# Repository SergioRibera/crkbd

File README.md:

# Corne keyboard

The Corne keyboard is a split keyboard with 3x6 column staggered keys
and 3 thumb keys, based on [Helix](https://github.com/MakotoKurauchi/helix).
Crkbd stands for Corne Keyboard.

## Latest versions
- corne-cherry: for Cherry MX compatible switches

  - v4 Hotswappable ([JP](docs/corne-cherry/v4/buildguide_jp.md)/[EN](docs/corne-cherry/v4/buildguide_en.md))
  - v4 Soldering (will be released)
- corne-chocolate: for Kailh choc v1 and v2 switches
  - v4 Hotswappable ([JP](docs/corne-chocolate/v4/buildguide_jp.md)/[EN](docs/corne-chocolate/v4/buildguide_en.md)):
  - v4 Soldering (will be released)

- [Corne v4 Cherry Wireless](./pcbs/cherry-wireless)

## Old versions

- corne-classic: for Cherry MX compatible switches 
  - v1 Soldering: ([JP](docs/corne-classic/buildguide_jp.md)/[EN](docs/corne-classic/buildguide_en.md))
- corne-cherry: for Cherry MX compatible switches
  - v2 Hotswappable: ([JP](docs/corne-cherry/v2/buildguide_jp.md)/[EN](docs/corne-cherry/v2/buildguide_en.md))
  - v2 Hotswappable tilting version: ([tilting, JP](docs/corne-cherry/v2/buildguide_tilting_tenting_plate_jp.md)/[tilting, EN](docs/corne-cherry/v2/buildguide_tilting_tenting_plate_en.md)):
  - v3 Hotswappable: ([JP](docs/corne-cherry/v3/buildguide_jp.md)/[EN](docs/corne-cherry/v3/buildguide_en.md))
- corne-chocolate: for Kailh choc v1 switches
  - v2 Hotswappable: ([JP](docs/corne-chocolate/v2/buildguide_jp.md)/[EN](docs/corne-chocolate/v2/buildguide_en.md)):
- corne-light: for easy build with a simple PCB
  - v1 Soldering: ([JP](docs/corne-light/v1/buildguide_jp.md)/[EN](docs/corne-light/v1/buildguide_en.md)):
  - v2 Soldering: ([JP](docs/corne-light/v2/buildguide_low_edition_jp.md)/[EN](docs/corne-light/v2/buildguide_low_edition_en.md)):

## Images

### Cherry

### Chocolate

### Drawing

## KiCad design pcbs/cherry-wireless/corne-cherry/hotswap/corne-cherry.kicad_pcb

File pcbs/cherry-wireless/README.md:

# Corne Keyboard Wireless Fork

This project is a customized fork of the popular Corne ergonomic keyboard.

> [!NOTE]
> As soon as I have my build I will upload pictures of the finished keyboard.

## Disclaimer

> [!IMPORTANT]
> **⚠️ IMPORTANT NOTICE: I am not an electronics expert ⚠️**
>
> This project has been carried out with the help of a professional contracted through Fiverr.
> If you have specific technical questions, I recommend consulting an expert.
>
> https://fiverr.com/pcbdesign_engr

## Features

- Custom layout based on the original Corne
- Hotswap Sockets
- Sk6812MiniE RGB LED per switch
- NRF52840-QIAA-R7 Microcontroller
- Differential pair routing from USB to MCU
- TypeC USB
- NiceView connector
- Removed extra keys added in v4
- Removed TRRS?

> [!NOTE]
> According to the engineer in charge, all components available at LCSC JLCPCB were used.

## Project Images

## Acknowledgements

This project would not have been possible without the help of a talented Fiverr professional. You can find their profile here: https://fiverr.com/pcbdesign_engr

I would also like to thank the original Corne Keyboard community for their incredible work and for inspiring this project.

## License

Use it as you wish, subject to the license of the original project.

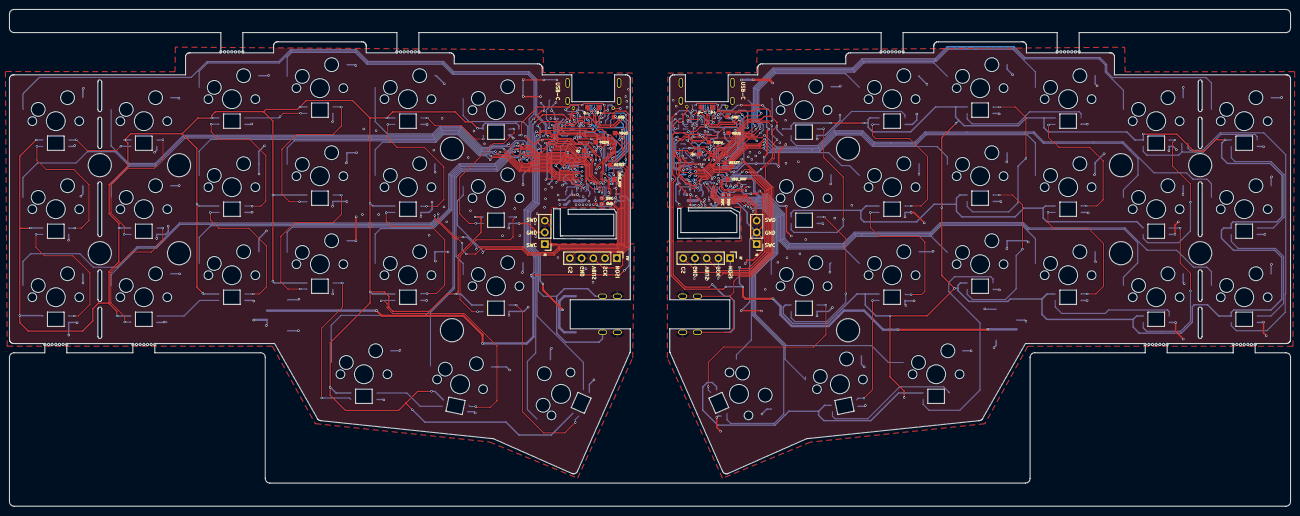
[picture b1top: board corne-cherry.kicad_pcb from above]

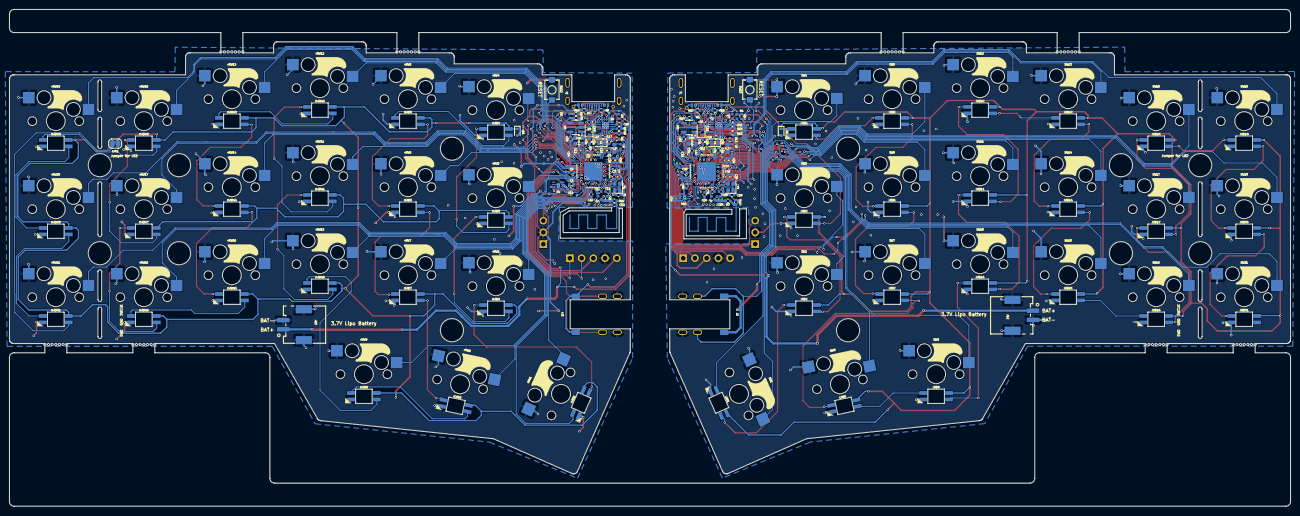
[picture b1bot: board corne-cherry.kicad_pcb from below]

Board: 2 copper layers, 277.2 x 107.5 mm, 233 parts (201 on the bottom side), 179 nets.

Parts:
AE1, AE2: Antenna; 2.4GHz-meander-antenna-v2
BT1, BT2, BT3, BT4: Breakaway Tabs; Breakaway_Tabs
C1, C13, C14, C20, C24, C25, C26, C35, C36, C41, C46, C50, C51, C52: 4.7uF; C_0402_1005Metric
C2, C3, C4, C10, C19, C32, C42, C43, C44, C45: 100nF; C_0402_1005Metric
C5, C9, C28, C31: 1pF; C_0402_1005Metric
C6, C7, C17, C18, C29, C30, C39, C40: 15pF; C_0402_1005Metric
C8, C15, C23, C37, C47, C49: 1uF; C_0402_1005Metric
C11, C33: 100pF; C_0402_1005Metric
C12, C34: 1nF; C_0402_1005Metric
C16, C38: 47nF; C_0402_1005Metric
C21, C48: 10uF; C_0603_1608Metric
C22, C27: 1.5pF; C_0402_1005Metric
D1: 1N4148WT; D_SOD-523
D2, D4: BLUE; LED_0402_1005Metric
D3, D7: ORANGE; LED_0402_1005Metric
D5, D6: PMEG4010CEJ; D_SOD-323F
J1, J7: USB_C_Receptacle_USB2.0; USB-C_C168688
J2: TRS; PJ-398A-5A_PJ-399B-6A
J3, J11: Screw_Terminal_01x05; PinHeader_1x05_P2.54mm_Vertical
J4, J5, J9, J10: PTH; PTH-0.8_0.45mm
J6, J8: Conn_01x03; PinHeader_1x03_P2.54mm_Vertical
J12, J13: Conn_01x02_Shielded; CONN-SMD_SM02B-PASS-TLFSN
L1, L5: 3.9nH; L_0402_1005Metric
L2, L6: 15nH; L_0402_1005Metric
L3, L4, L7, L8: 10uH; L_0603_1608Metric
LED1, LED2, LED3, LED4, LED5, LED6, LED7, LED8, LED9, LED10, LED11, LED12, LED13, LED14, LED15, LED16, LED17, LED18, LED19, LED20, LED21: YS-SK6812MINI-E; YS-SK6812MINI-E_crone
NT1, NT2: NetTie_2; net-tie-2-tiny
R1, R13: 3.9k; R_0402_1005Metric
R2, R14: 2M; R_0402_1005Metric
R3, R11: 0R; R_0402_1005Metric
R4, R5: 1.5k; R_0402_1005Metric
R6, R7, R8, R12, R15, R18: 10k; R_0402_1005Metric
R9, R10, R16, R17: 5.1k; R_0402_1005Metric
SW1: SW_Push; keyswitch_cherrymx_hotswap_1.5u
SW2, SW3, SW4, SW5, SW6, SW7, SW8, SW9, SW10, SW11, SW12, SW13, SW14, SW15, SW16, SW17, SW18, SW19, SW20, SW21: SW_Push; keyswitch_cherrymx_hotswap_1u
SW22, SW23: SW_SPST; SW-SMD-TS-1088-AR02016
TP1, TP2, TP3, TP4, TP5, TP6, TP7, TP8, TP9, TP10, TP11, TP12, TP13, TP14, TP15, TP16, TP17, TP18, TP19, TP20: PAD; TestPoint_Pad_1.0x1.0mm-nosilk
U1, U4: NRF52840-QIAA-R7; AQFN-73-1EP_7x7mm_P0.5mm_NRF52840-custom
U2, U7: BQ24075RGT; VQFN-16-1EP_3x3mm_P0.5mm_EP1.6x1.6mm
U3, U8: XC6220B331MR; TSOT-23-5
U5, U9: ESDR0502NMUTAG; UDFN-6_1.2x1.0mm_P0.4mm
U6, U10: MAX17048; TDFN-8-1EP_2x2mm_P0.5mm_EP0.8x1.2mm
Y1, Y3: 32MHz; Crystal_SMD_2016-4Pin_2.0x1.6mm
Y2, Y4: 32.768 kHz; Crystal_SMD_2012-2Pin_2.0x1.2mm
rBT1, rBT2, rBT3, rBT4: Breakaway Tabs; Breakaway_Tabs
rD1: 1N4148WT; D_SOD-523
rJ2: TRS; PJ-398A-5A_PJ-399B-6A
rJP1: SolderJumper_2_Bridged; SolderJumper-2_P1.3mm_Open_RoundedPad1.0x1.5mm
rLED1, rLED2, rLED3, rLED4, rLED5, rLED6, rLED7, rLED8, rLED9, rLED10, rLED11, rLED12, rLED13, rLED14, rLED15, rLED16, rLED17, rLED18, rLED19, rLED20, rLED21: YS-SK6812MINI-E; YS-SK6812MINI-E_crone
rSW1: SW_Push; keyswitch_cherrymx_hotswap_1.5u
rSW2, rSW3, rSW4, rSW5, rSW6, rSW7, rSW8, rSW9, rSW10, rSW11, rSW12, rSW13, rSW14, rSW15, rSW16, rSW17, rSW18, rSW19, rSW20, rSW21: SW_Push; keyswitch_cherrymx_hotswap_1u

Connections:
/left/ANT_L: AE2.1 (A), C27.2, R3.2
/left/CC1: J7.A5 (CC1), R16.1
/left/CC2: J7.B5 (CC2), R17.1
/left/KEY1_L: SW1.1, U4.AC21 (P0.25)
/left/KEY2_L: SW2.1, U4.T23 (P1.05)
/left/KEY3_L: SW3.1, U4.AD18 (P0.22)
/left/KEY4_L: SW4.1, U4.A8 (AIN7/P0.31)
/left/KEY5_L: SW5.1, U4.A10 (AIN5/P0.29)
/left/KEY6_L: SW6.1, U4.A20 (P1.10)
/left/KEY7_L: SW7.1, U4.R24 (P1.06)
/left/KEY8_L: SW8.1, U4.V23 (P1.03)
/left/KEY9_L: SW9.1, U4.P23 (P1.07)
/left/KEY10_L: SW10.1, U4.U24 (P1.04)
/left/KEY11_L: SW11.1, U4.B19 (P1.11)
/left/KEY12_L: SW12.1, U4.A12 (AIN0/P0.02)
/left/KEY13_L: SW13.1, U4.U1 (TRACEDATA1/P0.12)
/left/KEY14_L: SW14.1, U4.B17 (P1.12)
/left/KEY15_L: SW15.1, U4.W24 (P1.02)
/left/KEY16_L: SW16.1, U4.AD22 (TRACEDATA0/P1.00)
/left/KEY17_L: SW17.1, U4.A16 (P1.13)
/left/KEY18_L: SW18.1, U4.B9 (AIN6/P0.30)
/left/KEY19_L: SW19.1, U4.P2 (P1.08)
/left/KEY20_L: SW20.1, U4.B13 (AIN1/P0.03)
/left/KEY21_L: SW21.1, U4.AD20 (P0.24)
/left/RGBLEDs_L: LED1.4 (DIN), U4.Y23 (P1.01)
/right/ANT_R: AE1.1 (A), C22.2, R11.2
/right/CC1: J1.A5 (CC1), R9.1
/right/CC2: J1.B5 (CC2), R10.1
/right/KEY1_R: U1.AC21 (P0.25), rSW1.1
/right/KEY2_R: U1.T23 (P1.05), rSW2.1
/right/KEY3_R: U1.AD18 (P0.22), rSW3.1
/right/KEY4_R: U1.A8 (AIN7/P0.31), rSW4.1
/right/KEY5_R: U1.A10 (AIN5/P0.29), rSW5.1
/right/KEY6_R: U1.A20 (P1.10), rSW6.1
/right/KEY7_R: U1.R24 (P1.06), rSW7.1
/right/KEY8_R: U1.V23 (P1.03), rSW8.1
/right/KEY9_R: U1.P23 (P1.07), rSW9.1
/right/KEY10_R: U1.U24 (P1.04), rSW10.1
/right/KEY11_R: U1.B19 (P1.11), rSW11.1
/right/KEY12_R: U1.A12 (AIN0/P0.02), rSW12.1
/right/KEY13_R: U1.U1 (TRACEDATA1/P0.12), rSW13.1
/right/KEY14_R: U1.B17 (P1.12), rSW14.1
/right/KEY15_R: U1.W24 (P1.02), rSW15.1
/right/KEY16_R: U1.AD22 (TRACEDATA0/P1.00), rSW16.1
/right/KEY17_R: U1.A16 (P1.13), rSW17.1
/right/KEY18_R: U1.B9 (AIN6/P0.30), rSW18.1
/right/KEY19_R: U1.P2 (P1.08), rSW19.1
/right/KEY20_R: U1.B13 (AIN1/P0.03), rSW20.1
/right/KEY21_R: U1.AD20 (P0.24), rSW21.1
/right/RGBLEDs_R: U1.Y23 (P1.01), rLED1.4 (DIN)
/right/TX_R: U1.L1 (P0.06), rJ2.R
BAT_I2C_SCL_L: U4.AC15 (P0.19), U10.7 (SCL)
BAT_I2C_SCL_R: U1.AC15 (P0.19), U6.7 (SCL)
BAT_I2C_SDA_L: U4.AC19 (P0.23), U10.8 (SDA)
BAT_I2C_SDA_R: U1.AC19 (P0.23), U6.8 (SDA)
BLUE_LED_L: D4.2 (A), U4.K2 (AIN3/P0.05)
BLUE_LED_R: D2.2 (A), U1.K2 (AIN3/P0.05)
CHARGE_CTRL_1_L: R12.1, U4.G1 (P0.26)
CHARGE_CTRL_1_R: R7.1, U1.G1 (P0.26)
CHARGE_CTRL_2_L: R13.2, U4.A14 (P1.15)
CHARGE_CTRL_2_R: R1.2, U1.A14 (P1.15)
CS_L: J11.5, U4.AD16 (P0.20)
CS_R: J3.5, U1.AD16 (P0.20)
EXT_5V_L: C49.1, D6.1 (K), J2.T, U7.13 (IN)
EXT_5V_R: C23.1, D5.1 (K), U2.13 (IN), rJ2.T
EXT_VCC_L: C50.2, U8.5 (VOUT)
EXT_VCC_R: C20.2, U3.5 (VOUT)
GND: C27.1, C28.1, C29.2, C30.2, C32.2, C33.2, C34.2, C35.2, C36.1, C37.1, C38.1, C39.1, C40.1, C41.1, C42.1, C43.1, C44.1, C45.1, C46.1, C47.1, C48.1, C49.2, C50.1, C51.1, C52.1, J2.S, J7.A1 (GND), J8.2, J10.1, J11.4, J12.2, J12.SH (Shield), LED1.3 (VSS), LED2.3 (VSS), LED3.3 (VSS), LED4.3 (VSS), LED5.3 (VSS), LED6.3 (VSS), LED7.3 (VSS), LED8.3 (VSS), LED9.3 (VSS), LED10.3 (VSS), LED11.3 (VSS), LED12.3 (VSS), LED13.3 (VSS), LED14.3 (VSS), LED15.3 (VSS), LED16.3 (VSS), LED17.3 (VSS), LED18.3 (VSS), LED19.3 (VSS), LED20.3 (VSS), LED21.3 (VSS), NT2.2, R4.1, R14.2, R16.2, R17.2, R18.2, SW1.2, SW2.2, SW3.2, SW4.2, SW5.2, SW6.2, SW7.2, SW8.2, SW9.2, SW10.2, SW11.2, SW12.2, SW13.2, SW14.2, SW15.2, SW16.2, SW17.2, SW18.2, SW19.2, SW20.2, SW21.2, SW23.2 (B), TP13.1, U4.B7 (VSS), U4.EP (VSS), U7.4 (~CE), U7.5 (EN2), U7.8 (VSS), U7.15 (SYSOFF), U7.17 (VSS), U8.2 (GND), U9.1 (GND), U10.1 (CTG), U10.4 (GND), U10.6 (QSTRT), U10.9 (EP), Y3.2, Y3.4
GNDR: C1.1, C2.1, C3.1, C4.1, C5.1, C6.2, C7.2, C8.1, C10.2, C11.2, C12.2, C13.2, C14.1, C15.1, C16.1, C17.1, C18.1, C19.1, C20.1, C21.1, C22.1, C23.2, C24.1, C25.1, C26.1, J1.A1 (GND), J3.4, J5.1, J6.2, J13.2, J13.SH (Shield), NT1.2, R2.2, R5.1, R8.2, R9.2, R10.2, SW22.2 (B), TP5.1, U1.B7 (VSS), U1.EP (VSS), U2.4 (~CE), U2.5 (EN2), U2.8 (VSS), U2.15 (SYSOFF), U2.17 (VSS), U3.2 (GND), U5.1 (GND), U6.1 (CTG), U6.4 (GND), U6.6 (QSTRT), U6.9 (EP), Y1.2, Y1.4, rJ2.S, rLED1.3 (VSS), rLED2.3 (VSS), rLED3.3 (VSS), rLED4.3 (VSS), rLED5.3 (VSS), rLED6.3 (VSS), rLED7.3 (VSS), rLED8.3 (VSS), rLED9.3 (VSS), rLED10.3 (VSS), rLED11.3 (VSS), rLED12.3 (VSS), rLED13.3 (VSS), rLED14.3 (VSS), rLED15.3 (VSS), rLED16.3 (VSS), rLED17.3 (VSS), rLED18.3 (VSS), rLED19.3 (VSS), rLED20.3 (VSS), rLED21.3 (VSS), rSW1.2, rSW2.2, rSW3.2, rSW4.2, rSW5.2, rSW6.2, rSW7.2, rSW8.2, rSW9.2, rSW10.2, rSW11.2, rSW12.2, rSW13.2, rSW14.2, rSW15.2, rSW16.2, rSW17.2, rSW18.2, rSW19.2, rSW20.2, rSW21.2
L_USB_D+: J7.A6 (D+), J7.B6 (D+), TP15.1, U4.AD6 (D+), U9.5 (D+)
L_USB_D-: J7.A7 (D-), J7.B7 (D-), TP14.1, U4.AD4 (D-), U9.4 (D-)
MOSI_L: J11.1, U4.AD10 (P0.15)
MOSI_R: J3.1, U1.AD10 (P0.15)
unnamed: C5.2, L1.1, R11.1
unnamed: C28.2, L5.1, R3.1
unnamed: D1.1 (K), LED1.1 (VDD), LED2.1 (VDD), LED3.1 (VDD), LED4.1 (VDD), LED5.1 (VDD), LED6.1 (VDD), LED7.1 (VDD), LED8.1 (VDD), LED9.1 (VDD), LED10.1 (VDD), LED11.1 (VDD), LED12.1 (VDD), LED13.1 (VDD), LED14.1 (VDD), LED15.1 (VDD), LED16.1 (VDD), LED17.1 (VDD), LED18.1 (VDD), LED19.1 (VDD), LED20.1 (VDD), LED21.1 (VDD)
unnamed: D2.1 (K), R5.2
unnamed: D3.2 (A), R6.2
unnamed: D3.1 (K), U2.9 (~CHG)
unnamed: D4.1 (K), R4.2
unnamed: D7.2 (A), R15.2
unnamed: D7.1 (K), U7.9 (~CHG)
unnamed: L2.2, L3.1
unnamed: L6.2, L7.1
unnamed: LED1.2 (DOUT), LED2.4 (DIN)
unnamed: LED2.2 (DOUT), LED3.4 (DIN)
unnamed: LED3.2 (DOUT), LED4.4 (DIN)
unnamed: LED4.2 (DOUT), LED5.4 (DIN)
unnamed: LED5.2 (DOUT), LED6.4 (DIN)
unnamed: LED6.2 (DOUT), LED7.4 (DIN)
unnamed: LED7.2 (DOUT), LED8.4 (DIN)
unnamed: LED8.2 (DOUT), LED9.4 (DIN)
unnamed: LED9.2 (DOUT), LED10.4 (DIN)
unnamed: LED10.2 (DOUT), LED11.4 (DIN)
unnamed: LED11.2 (DOUT), LED12.4 (DIN)
unnamed: LED12.2 (DOUT), LED13.4 (DIN)
unnamed: LED13.2 (DOUT), LED14.4 (DIN)
unnamed: LED14.2 (DOUT), LED15.4 (DIN)
unnamed: LED15.2 (DOUT), LED16.4 (DIN)
unnamed: LED16.2 (DOUT), LED17.4 (DIN)
unnamed: LED17.2 (DOUT), LED18.4 (DIN)
unnamed: LED18.2 (DOUT), LED19.4 (DIN)
unnamed: LED19.2 (DOUT), LED20.4 (DIN)
unnamed: LED20.2 (DOUT), LED21.4 (DIN)
unnamed: C9.2, L1.2, U1.H23 (ANT)
unnamed: L3.2, U1.B3 (DCC)
unnamed: L4.2, U1.AB2 (DCCH)
unnamed: C10.1, U1.C1 (DEC1)
unnamed: C11.1, U1.D23 (DEC3)
unnamed: C15.2, C16.2, L2.1, U1.B5 (DEC4), U1.E24 (DEC6)
unnamed: C12.1, U1.N24 (DEC5)
unnamed: C13.1, U1.AC5 (DECUSB)
unnamed: C6.1, U1.B24 (XC1), Y1.1
unnamed: C7.1, U1.A23 (XC2), Y1.3
unnamed: C17.2, U1.D2 (XL1/P0.00), Y2.1
unnamed: C18.2, U1.F2 (XL2/P0.01), Y2.2
unnamed: R1.1, R7.2, U2.16 (ISET)
unnamed: R8.1, U2.1 (TS)
unnamed: C31.2, L5.2, U4.H23 (ANT)
unnamed: L7.2, U4.B3 (DCC)
unnamed: L8.2, U4.AB2 (DCCH)
unnamed: C32.1, U4.C1 (DEC1)
unnamed: C33.1, U4.D23 (DEC3)
unnamed: C37.2, C38.2, L6.1, U4.B5 (DEC4), U4.E24 (DEC6)
unnamed: C34.1, U4.N24 (DEC5)
unnamed: C35.1, U4.AC5 (DECUSB)
unnamed: C29.1, U4.B24 (XC1), Y3.1
unnamed: C30.1, U4.A23 (XC2), Y3.3
unnamed: C39.2, U4.D2 (XL1/P0.00), Y4.1
unnamed: C40.2, U4.F2 (XL2/P0.01), Y4.2
unnamed: R12.2, R13.1, U7.16 (ISET)
unnamed: R18.1, U7.1 (TS)
unnamed: rD1.1 (K), rLED1.1 (VDD), rLED2.1 (VDD), rLED3.1 (VDD), rLED4.1 (VDD), rLED5.1 (VDD), rLED6.1 (VDD), rLED7.1 (VDD), rLED8.1 (VDD), rLED9.1 (VDD), rLED10.1 (VDD), rLED11.1 (VDD), rLED12.1 (VDD), rLED13.1 (VDD), rLED14.1 (VDD), rLED15.1 (VDD), rLED16.1 (VDD), rLED17.1 (VDD), rLED18.1 (VDD), rLED19.1 (VDD), rLED20.1 (VDD), rLED21.1 (VDD)
unnamed: rJP1.1 (A), rLED18.2 (DOUT), rLED19.4 (DIN)
unnamed: rJP1.2 (B), rLED21.2 (DOUT)
unnamed: rLED1.2 (DOUT), rLED2.4 (DIN)
unnamed: rLED2.2 (DOUT), rLED3.4 (DIN)
unnamed: rLED3.2 (DOUT), rLED4.4 (DIN)
unnamed: rLED4.2 (DOUT), rLED5.4 (DIN)
unnamed: rLED5.2 (DOUT), rLED6.4 (DIN)
unnamed: rLED6.2 (DOUT), rLED7.4 (DIN)
unnamed: rLED7.2 (DOUT), rLED8.4 (DIN)
unnamed: rLED8.2 (DOUT), rLED9.4 (DIN)
unnamed: rLED9.2 (DOUT), rLED10.4 (DIN)
unnamed: rLED10.2 (DOUT), rLED11.4 (DIN)
unnamed: rLED11.2 (DOUT), rLED12.4 (DIN)
unnamed: rLED12.2 (DOUT), rLED13.4 (DIN)
unnamed: rLED13.2 (DOUT), rLED14.4 (DIN)
unnamed: rLED14.2 (DOUT), rLED15.4 (DIN)
unnamed: rLED15.2 (DOUT), rLED16.4 (DIN)
unnamed: rLED16.2 (DOUT), rLED17.4 (DIN)
unnamed: rLED17.2 (DOUT), rLED18.4 (DIN)
unnamed: rLED19.2 (DOUT), rLED20.4 (DIN)
unnamed: rLED20.2 (DOUT), rLED21.4 (DIN)
POWER_PIN_L: R14.1, U4.AD12 (P0.17), U8.3 (CE)
POWER_PIN_R: R2.1, U1.AD12 (P0.17), U3.3 (CE)
RESET_L: SW23.1 (A), TP18.1, U4.AC9 (P0.14), U4.AC11 (P0.16), U4.AC13 (P0.18/~RESET)
RESET_R: SW22.1 (A), TP17.1, U1.AC9 (P0.14), U1.AC11 (P0.16), U1.AC13 (P0.18/~RESET)
R_USB_D+: J1.A6 (D+), J1.B6 (D+), TP6.1, U1.AD6 (D+), U5.5 (D+)
R_USB_D-: J1.A7 (D-), J1.B7 (D-), TP4.1, U1.AD4 (D-), U5.4 (D-)
Rx_L: TP20.1, U4.J1 (AIN2/P0.04)
Rx_R: TP19.1, U1.J1 (AIN2/P0.04)
SCK_L: J11.2, U4.AD8 (P0.13)
SCK_R: J3.2, U1.AD8 (P0.13)
SWC_L: J8.1, TP10.1, U4.AA24 (SWDCLK)
SWC_R: J6.1, TP1.1, U1.AA24 (SWDCLK)
SWD_L: J8.3, TP11.1, U4.AC24 (SWDIO)
SWD_R: J6.3, TP2.1, U1.AC24 (SWDIO)
Tx_L: J2.R, U4.L1 (P0.06)
VBAT_L: C43.2, C52.2, J9.1, J12.1, U7.2 (BAT), U7.3 (BAT), U10.2 (CELL), U10.3 (VDD)
VBAT_R: C19.2, C26.2, J4.1, J13.1, U2.2 (BAT), U2.3 (BAT), U6.2 (CELL), U6.3 (VDD)
VBUS_L: C36.2, D1.2 (A), D6.2 (A), J7.A4 (VBUS), J11.3, TP16.1, U4.AD2 (VBUS), U9.6 (VBUS)
VBUS_R: C14.2, D5.2 (A), J1.A4 (VBUS), J3.3, TP8.1, U1.AD2 (VBUS), U5.6 (VBUS), rD1.2 (A)
VDDH_L: C41.2, C48.2, C51.2, R15.1, TP12.1, U4.Y2 (VDDH), U7.6 (EN1), U7.10 (OUT), U7.11 (OUT), U8.1 (VIN)
VDDH_R: C21.2, C24.2, C25.2, R6.1, TP7.1, U1.Y2 (VDDH), U2.6 (EN1), U2.10 (OUT), U2.11 (OUT), U3.1 (VIN)
VDD_NRF_L: C42.2, C44.2, C45.2, C46.2, C47.2, L8.1, TP9.1, U4.A22 (VDD), U4.AD14 (VDD), U4.AD23 (VDD), U4.B1 (VDD), U4.W1 (VDD)
VDD_NRF_R: C1.2, C2.2, C3.2, C4.2, C8.2, L4.1, TP3.1, U1.A22 (VDD), U1.AD14 (VDD), U1.AD23 (VDD), U1.B1 (VDD), U1.W1 (VDD)
VSS_PA_L: C31.1, NT2.1, U4.F23 (VSS_PA)
VSS_PA_R: C9.1, NT1.1, U1.F23 (VSS_PA)

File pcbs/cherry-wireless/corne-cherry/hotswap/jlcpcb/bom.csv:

Designator,Footprint,Quantity,Value,LCSC Part #
"BT1, BT2, BT3, BT4, rBT1, rBT2, rBT3, rBT4",Breakaway_Tabs,8,Breakaway Tabs,
"C1, C13, C14, C24, C25, C26, C35, C36, C41, C46, C51, C52",0402,12,4.7uF,C23733
"C10, C2, C3, C32, C4, C42, C44, C45",0402,8,100nF,C307331
"C11, C33",0402,2,100pF,C1546
"C12, C34",0402,2,1nF,C1523
"C15, C23, C37, C47, C49, C8",0402,6,1uF,C52923
"C16, C38",0402,2,47nF,C312032
"C17, C18, C29, C30, C39, C40, C6, C7",0402,8,15pF,C1548
"C19, C43",0402,2,100nF,C1525
"C20, C50",0402,2,4.7uF, 
"C21, C48",0603,2,10uF,C19702
"C22, C27",0402,2,1.5pF,C1552
"C28, C31, C5, C9",0402,4,1pF,C1550
"D1, rD1",D_SOD-523,2,1N4148WT,
"D2, D4",0402,2,BLUE,C364550
"D3, D7",0402,2,ORANGE,C364554
"D5, D6",D_SOD-323F,2,PMEG4010CEJ,C50704
"J1, J7",USB-C_C168688,2,USB_C_Receptacle_USB2.0,C168688
"J11, J3",PinHeader_1x05_P2.54mm_Vertical,2,Screw_Terminal_01x05,
"J12, J13",CONN-SMD_SM02B-PASS-TLFSN,2,Conn_01x02_Shielded,
"J2, rJ2",PJ-398A-5A_PJ-399B-6A,2,TRS,
"J6, J8",PinHeader_1x03_P2.54mm_Vertical,2,Conn_01x03,
"L1, L5",0402,2,3.9nH,C14033
"L2, L6",0402,2,15nH,C27143
"L3, L4, L7, L8",0603,4,10uH,C1035
"LED1, LED10, LED11, LED12, LED13, LED14, LED15, LED16, LED17, LED18, LED19, LED2, LED20, LED21, LED3, LED4, LED5, LED6, LED7, LED8, LED9, rLED1, rLED10, rLED11, rLED12, rLED13, rLED14, rLED15, rLED16, rLED17, rLED18, rLED19, rLED2, rLED20, rLED21, rLED3, rLED4, rLED5, rLED6, rLED7, rLED8, rLED9",YS-SK6812MINI-E_crone,42,YS-SK6812MINI-E,C5149201
"NT1, NT2",net-tie-2-tiny,2,NetTie_2,
"R1, R13",0402,2,3.9k,C131467
"R10, R16, R17, R9",0402,4,5.1k,C105872
"R11, R3",0402,2,0R,C17168
"R12, R15, R18, R6, R7, R8",0402,6,10k,C25744
"R14, R2",0402,2,2M,C138014
"R4, R5",0402,2,1.5k,C114759
"SW1, rSW1",keyswitch_cherrymx_hotswap_1.5u,2,SW_Push,C2803348
"SW10, SW11, SW12, SW13, SW14, SW15, SW16, SW17, SW18, SW19, SW2, SW20, SW21, SW3, SW4, SW5, SW6, SW7, SW8, SW9, rSW10, rSW11, rSW12, rSW13, rSW14, rSW15, rSW16, rSW17, rSW18, rSW19, rSW2, rSW20, rSW21, rSW3, rSW4, rSW5, rSW6, rSW7, rSW8, rSW9",keyswitch_cherrymx_hotswap_1u,40,SW_Push,C2803348
"SW22, SW23",SW-SMD-TS-1088-AR02016,2,SW_SPST,
"U1, U4",AQFN-73-1EP_7x7mm_P0.5mm_NRF52840-custom,2, NRF52840-QIAA-R7,C190794
"U10, U6",TDFN-8-1EP_2x2mm_P0.5mm_EP0.8x1.2mm,2,MAX17048,C2682616
"U2, U7",VQFN-16-1EP_3x3mm_P0.5mm_EP1.6x1.6mm,2,BQ24075RGT,C2865459
"U3, U8",TSOT-23-5,2,XC6220B331MR,C86534
"U5, U9",UDFN-6_1.2x1.0mm_P0.4mm,2,ESDR0502NMUTAG,C94372
"Y1, Y3",Crystal_SMD_2016-4Pin_2.0x1.6mm,2,32MHz,C255896
"Y2, Y4",Crystal_SMD_2012-2Pin_2.0x1.2mm,2,32.768 kHz,C97607
rJP1,SolderJumper-2_P1.3mm_Open_RoundedPad1.0x1.5mm,1,SolderJumper_2_Bridged,

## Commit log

2024-08-09 add corne cherry wireless
2024-08-10 update corne cherry wireless
